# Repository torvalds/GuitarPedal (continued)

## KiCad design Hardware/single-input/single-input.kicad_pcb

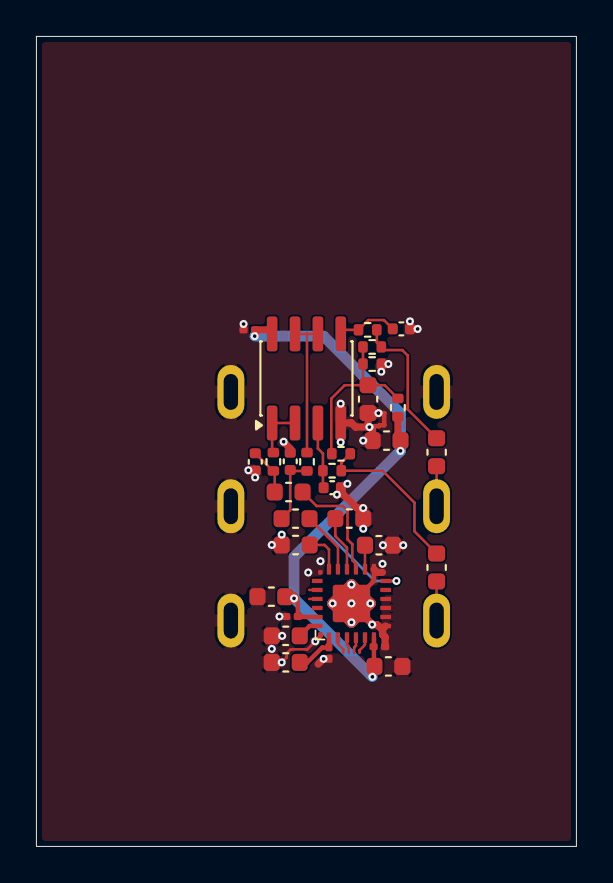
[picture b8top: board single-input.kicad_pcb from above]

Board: 4 copper layers, 30.0 x 45.0 mm, 32 parts (1 on the bottom side), 20 nets.

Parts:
C903, C904, C906, C907, C910, C911, C912, C922, C923: 2.2uF; C_0603_1608Metric
C905, C918, C919, C921: 0.1uF; C_0201_0603Metric
C908, C913: 150pF; C_0402_1005Metric
C909, C914: 2.2nF; C_0402_1005Metric
C915, C916, C917, C920: 10uF; C_0603_1608Metric
J901: AudioJack3_SwitchTR; NRJ6HM-1-PRE
R901, R902, R907, R908: 100R; R_0402_1005Metric
R903, R904, R905, R906: 1MEG; R_0402_1005Metric
U902: OPA2365AIDR; SOIC-8_3.9x4.9mm_P1.27mm
U903: TAC5242

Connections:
+3.3VA: C905.2, C915.1, C916.1, C917.1, C918.1, C919.1, R904.1, U902.8 (V+), U903.6 (IOVDD), U903.12 (MD5), U903.23 (AVDD)
/DREG: C920.1, C921.1, U903.1 (DREG)
/IN1M: C903.2, U903.16 (IN1M)
/IN1P: C907.2, U903.15 (IN1P)
/IN2M: C904.2, U903.18 (IN2M)
/IN2P: C912.2, U903.17 (IN2P)
/IN^{LEFT}: C906.1, J901.T
/IN^{RIGHT}: C911.1, J901.R
/MICBIAS: C923.1, U903.14 (MICBIAS)
/VREF: C922.1, U903.24 (VREF)
GND: C903.1, C904.1, C905.1, C908.2, C909.1, C910.1, C913.2, C914.1, C915.2, C916.2, C917.2, C918.2, C919.2, C920.2, C921.2, C922.2, C923.2, J901.RN, J901.S, J901.TN, R905.2, U902.4 (V-), U903.7 (MD1), U903.8 (MD2), U903.9 (MD3), U903.10 (MD4), U903.13 (MD0), U903.A1 (GND), U903.A2 (GND), U903.A3 (GND), U903.A4 (GND), U903.PAD (GND)
unnamed: C906.2, R901.1, R903.2
unnamed: C907.1, C909.2, R902.2
unnamed: C910.2, R903.1, R904.2, R905.1, R906.2
unnamed: C911.2, R906.1, R907.1
unnamed: C912.1, C914.2, R908.2
unnamed: C908.1, R901.2, U902.3 (+)
unnamed: R902.1, U902.1, U902.2 (-)
unnamed: C913.1, R907.2, U902.5 (+)
unnamed: R908.1, U902.6 (-), U902.7
